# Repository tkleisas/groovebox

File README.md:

# groovebox — ВОКОИТЕР / ΟΡΓΑΝΟ

**Mission:** an open hardware and software groovebox that can be serviced
indefinitely. If a subsystem becomes unavailable, an equivalent one can be
substituted without discarding the panel, power system, enclosure, or
software. The reference brain is a **Raspberry Pi Zero 2W** on a replaceable
carrier, running the [yawn](https://github.com/tkleisas/yawn) audio engine;
a **Raspberry Pi Pico** panel module presents the whole control surface to
the brain as a plain USB-MIDI device.

Each SBC gets its own brain carrier and its own validated software profile;
the panel, power board, battery, and enclosure are the common platform. See
[`docs/mission.md`](docs/mission.md) for the mission, support tiers, and the
honest path for future Radxa/Orange Pi carriers.

Design language: Soviet-cosmonaut mission control per
[bokontep.gr](https://www.bokontep.gr) — deep-red faceplate, cream/black
keys, bilingual Greek/Cyrillic UI strings, terminal-green telemetry.

*Exploded NSR-1 rev B2 assembly, rendered in Blender. More views and the
[15-second detail animation](docs/renders/nsr1_animation.mp4):
[`docs/renders/`](docs/renders/).*

## Two designs, one repo

| | NSR-1 (ΟΡΓΑΝΟ 1) | NSR-2 |
|---|---|---|
| Concept | full-size panel, 400 × 170 mm | compact, 180 × 210 mm faceplate PCB |
| Keys | 55 MX keys (piano + 16-step row + function) | 45 Choc keys (4×8 grid) + 13 function |
| Control | 8 encoders, 2 pots, data slider, thumbstick | 4 encoders, thumbstick, crossfader |
| Status | **active target.** rev B2 control/keyboard verified; Pi brain carrier routed; power board routed except four rev A airwires | **deferred.** schematic-complete reference design; not the current build |
| Docs | [`docs/design.md`](docs/design.md) + [`hardware/README.md`](hardware/README.md) | [`docs/nsr2-design.md`](docs/nsr2-design.md) + [`nsr2/README.md`](nsr2/README.md) |

## What it does (emulator, today)

- **4 tracks** × **1–256 step patterns** (default 16, 16-step paged window).
  Per-step: on/off, velocity (data slider), accent (black keys), pitch and
  gate (hold-step + encoders, synth track).
- **Play mode**: the keyboard row becomes a 2-octave chromatic keyboard,
  velocity from the slider, joystick = pitch bend / mod. REC-arm + play
  records quantized notes into the pattern. On **drum tracks**
  (DrumSynth/DrumRack/DrumSlop) the 27 keys instead walk the
  instrument's drum voices left→right (whites and interleaved blacks as
  one physical strip, position modulo voice count — wraps at the end,
  so every key always sounds); toasts show the voice name.
- **Sound**: yawn engine instruments (SubtractiveSynth, DrumRack, FM,
  Wavetable, Granular, …) + one insert FX slot per track (29 effect types).
- **Sampling**: SAMPLE page — record from mic/line-in, trim, normalize,
  assign to a drum pad; LOAD page browses samples.
- **Controls (NSR-1 rev B2)**: 2 dedicated pots (filter cutoff/resonance),
  8 encoders with push (4 pageable + 4 amp-ADSR), data slider, 2-axis
  spring-return thumbstick, transport, MODE, </>, 4 soft keys, dual SHIFT
  keys at the keyboard row ends, dedicated 16-step row.
- **UI**: Elektron-style monochrome, 3 themes (mono / red / green phosphor),
  ПОЕХАЛИ! boot splash, full widget library (sequencer, mixer, waveform,
  ADSR, FM-algo, spectrum, phase pie, tuner, file browser, virtual keyboard…).
- **Sync/IO**: DIN MIDI in/out, Ableton Link (engine), USB-MIDI on OTG,
  integrated mic + line in for sampling (WM8731 codec).

## Hardware (NSR-1, rev B2)

| | |
|---|---|
| Brain | Raspberry Pi Zero 2W on the first SBC-specific carrier; separate carriers planned per SBC |
| Panel controller | Raspberry Pi Pico — presents as USB-MIDI device `groovebox-panel` |
| Audio codec | Audio Injector Zero (WM8731: stereo out + mic/line in) on the Pi carrier. Bench rig: CJMCU-1334 (UDA1334A, playback only) |
| Display | 4.0" SPI TFT 480×320 (ILI9488); UI rendered at 240×160, 2× integer scale |
| Keys | 55 MX-style switches (Gateron Red / Silent Red), hot-swap sockets, 32 LEDs, 19.05 mm pitch |
| Panel I/O | 5× MCP23017 (55 keys + 8 encoder pushes), HT16K33 (32 LEDs), 2× ADS1115 (2 pots + slider + joystick) |
| Power | Separate 1S power/battery board (USB-C charger, power path, 5V/3A boost, fuel gauge); 5000 mAh target |
| Panel size | 400×170 mm, deep red |

Full hardware design, GPIO maps and BOM: [docs/design.md](docs/design.md).
New platform board specs: [Pi Zero 2W brain carrier](hardware/brain/netlist-spec.md)
and [power/battery board](hardware/power/netlist-spec.md).
Panel/brain protocol (USB-MIDI + SysEx config):
[docs/panel-protocol.md](docs/panel-protocol.md).

### NSR-1 PCB views

Bare-board 3D renders, top and bottom, for all four NSR-1 boards. Headers
and connectors carry silkscreen pin numbers; the Pico header also has GPIO
names. The Pi carrier and power board are rev A; the power board still has
four open airwires (two `BAT_NEG`, two `SCL`). Full-size images are in
[`docs/renders/pcb/`](docs/renders/pcb/).

| Board | Top | Bottom |
|---|---|---|
| Control |  |  |
| Keyboard |  |  |
| Pi brain carrier |  |  |
| Power/battery |  |  |

## ElectroMechanicalDesigner integration

The NSR-1 hardware is imported and validated with
[**ElectroMechanicalDesigner (EMD)**](https://github.com/tkleisas/ElectroMechanicalDesigner):

- `hardware/tools/export_netlist.py` exports KiCad XML netlists.
- `hardware/tools/verify_emd.py` imports all four netlists and routed PCBs
  (control, keyboard, Pi carrier, power), validates them, and builds a combined
  **237-part / 735-connection** project.
- The combined project is placed in the 400 × 170 mm panel envelope and its
  package is verified with `emd package verify`.
- Generated projects/packages live in `hardware/emd-packages/` (gitignored);
  regenerate with
  `python3 hardware/tools/verify_emd.py --combined hardware/emd-packages/groovebox.json --package-dir hardware/emd-packages`.

EMD also validates the KiCad ERC/DRC flow, mounting-hole mechanical ports, and
fabrication exports used by this repo.

## Architecture

```
  Pi Zero 2W on brain carrier             Pico (panel module)
  ├ yawn engine (I2S codec)      ◄─USB─►  ├ keys    (5× MCP23017)
  ├ fbdev UI → 480×320 SPI TFT            ├ LEDs    (HT16K33)
  ├ DIN MIDI in/out (UART)                ├ encoders (GPIO)
  └ mic (codec input)                     └ analog  (2× ADS1115)
            ▲ 5V / power signals
            │
  Power/battery board — USB-C charge, 1S pack, gauge, 5V boost
```

The panel is deliberately dumb — it reports physical events and accepts
routing SysEx; **all musical semantics live in the brain app**. The same
app binary runs on the PC (SDL3 emulator with a geometry-driven,
mouse-interactive virtual front panel) and on the Pi (fbdev + panel over
USB-MIDI) through a HAL, which is how everything is developed before
hardware exists. See [`docs/panel-protocol.md`](docs/panel-protocol.md)
for the wire protocol.

## Building

| Target | How | Needs |
|---|---|---|
| Emulator | CMake in `emulator/` (binary `groovebox_sim`) | MSVC or GCC, SDL3, yawn submodule (`git submodule update --init`) |
| Panel firmware | `panel-fw/build.ps1` or CMake with the Pico SDK (see `panel-fw/README.md`) | Pico SDK + toolchain |
| OS image | Raspberry Pi OS Lite + `os-image/customize/` (first-run script, systemd unit) | a Pi / imager |
| Hardware | KiCad 10; NSR-1 and NSR-2 schematics are **generated** — see [`hardware/README.md`](hardware/README.md) and [`nsr2/README.md`](nsr2/README.md) before touching them | KiCad 10.0+ |

Windows/MSVC emulator build:

```bash
CMAKE="/c/Program Files/Microsoft Visual Studio/2022/Community/Common7/IDE/CommonExtensions/Microsoft/CMake/CMake/bin/cmake.exe"
"$CMAKE" -B emulator/build -S emulator -G "Visual Studio 17 2022" -A x64
"$CMAKE" --build emulator/build --target groovebox_sim --config Debug -- -m
emulator/build/Debug/groovebox_sim.exe            # interactive sim
```

The yawn engine is built lean (VST3 / NAM / Link / 3D / ONNX / video OFF).

### Pi cross-build (arm64, Docker)

`tools/build-pi-arm64.sh` builds `groovebox_sim` for 64-bit Raspberry Pi
OS (bookworm, aarch64) in a Docker container — no Pi needed on the desk:

```bash
tools/build-pi-arm64.sh     # image + cross-build + provenance + qemu smoke
```

The image (`emulator/pi/Dockerfile`) is Debian bookworm with the
`aarch64-linux-gnu` toolchain and the **arm64** `libasound2-dev` (ALSA is
the one target-arch dependency — RtMidi and PortAudio are compiled from
source by yawn's FetchContent but link against the target's ALSA). The
toolchain file is `emulator/pi/aarch64-toolchain.cmake`; CMake is driven
with `-DGB_PI_BACKEND=ON`, which swaps the SDL3 SimBackend for the
headless PiBackend (fbdev + RtMidi) and drops the SDL3 link. The script
finishes by proving the binary (`readelf -h` → `AArch64`) and
smoke-running it under `qemu-aarch64` (the container has no ALSA device
PortAudio accepts, so the engine can't boot there — the qemu run proves
execution + graceful peripheral degradation; `--profile` numbers need a
Pi with a codec or the Windows sim).

### Pi backend (PiBackend, `GB_PI_BACKEND=ON`)

- **Display**: fbdev — opens `/dev/fb1` (ILI9488 SPI TFT via fbtft
  overlay), falls back to `/dev/fb0`, mmaps the framebuffer and writes
  the 240×160 RGB565 UI frame 2×-doubled (480×320), centered. 16 bpp
  writes through; 32 bpp (XRGB8888) converts per pixel.
- **Panel in**: RtMidi input on the port named `groovebox-panel`,
  decoded per [`docs/panel-protocol.md`](docs/panel-protocol.md)
  (channel 1: notes 36–91 → keys, CC 20/21 pots, CC 26 slider, CC 1
  joystick Y, CC 16–23 encoder deltas, CC 32–39 encoder push,
  pitch bend → joystick X).
- **LEDs**: note on/off on channel 2 back to the panel.
- Neither peripheral is fatal — a Pi booted without the panel or the
  display logs a warning and keeps the engine running (CI / profiling).
- SIGINT/SIGTERM route to the app's quit path, so the systemd unit or
  Ctrl-C shuts the engine down cleanly.

Deployment note: the arm64 binary dynamically links `libportaudio.so.2`
(yawn builds PortAudio shared). Ship `emulator/build-pi-arm64/lib/libportaudio.so.2`
alongside the binary (e.g. in `/usr/local/lib` + `ldconfig`, or next to
the binary with an rpath). `libasound.so.2` is part of Raspberry Pi OS.

### Heavy-load profiling (`--profile`)

```
groovebox_sim --profile 10
```

Worst-case musical load for the Zero 2W gate: all 4 tracks programmed on
all 16 steps (vel 120), 140 BPM, a reverb inserted on T1+T2, transport
rolling, UI rendering every frame. Prints PortAudio CPU% and the
PortAudio callback status flags (xrun bits) once per second, then exits
0. Runs on every backend (Windows sim, Pi hardware, qemu).

### Interactive controls (sim)

- **Mouse** (panel view): click keys/buttons; drag pots & slider; 2D-drag
  joystick (springs back); wheel over encoders; click encoder = push.
- **PC keyboard**: Z-row + Q-row = piano whites (with standard black-key
  letters/digits), Space = play/stop, Enter = rec, Tab = MODE,
  arrows = </>, F1–F4 = soft keys S1–S4, Shift = SHIFT, F5–F10 + `-`/`=` =
  pots, `[`/`]` = slider, F11 = panel/screen view, F12 = theme, ESC = quit.
- **Track select**: S3/S4 (TRK-/TRK+) or Shift + white keys 1–4;
  Shift + white 5–8 = mute.

### Drum editing (INST page on drum tracks)

For pad instruments (DrumSynth / DrumRack / DrumSlop) the INST page
edits the **last-played pad**: hitting a key in play mode (or a
hold-step voice p-lock) makes that voice the edit pad — the header
shows it (`SNARE T1 140`), an `EDIT SNARE` toast confirms, and all
bindings rebuild to that voice. Sequencer playback never steals the
edit focus.

- **Encoder pages**: PAD / PAD2 = the edited pad's params (DrumSynth:
  Tune/Drive, kick adds Sine/White/Pink; DrumRack: Pad Vol/Pan/Pitch/
  Choke/Start/End; DrumSlop: Pad Vol/Pan/Pitch/Rev/Cutoff/Reso),
  KIT = instrument globals (Volume, OS 2×, slice controls). S2 = PG+
  cycles them.
- **Macro encoders 5–8** (factory binding): A/D = the edited pad's
  attack/decay (S/R also bound on DrumSlop). Pots stay inert on
  DrumSynth/DrumRack (CUT/RES bind only where the instrument exposes
  them — DrumSlop pads).
- DrumSynth has no selected-slot concept — its 36 params are globally
  indexed per voice (kick = 7 @ index 0, others = 4 @ 7+(slot−1)·4),
  so the edit pad is pure index arithmetic; DrumRack/DrumSlop get the
  pad via their `selectedPad` setter.

### Scripted test / asset modes

```
groovebox_sim --smoke       engine boot + notes self-test
groovebox_sim --uitest      UI interaction assertions (8/8)
groovebox_sim --seqtest     sequencer scheduling assertions (6/6)
groovebox_sim --longtest    1–256 step pattern assertions (9/9)
groovebox_sim --paramtest   pot pickup / encoder ownership / FX (11/11)
groovebox_sim --sampletest  mic capture → trim → assign → browser (8/8)
groovebox_sim --panelprobe  synthetic mouse → HAL events (3/3)
groovebox_sim --panel=nsr2 --nsr2test    NSR-2 grid semantics (6/6)
groovebox_sim --revbtest    NSR-1 rev B: step row, p-lock, scale lock (6/6)
groovebox_sim --macrotest   macro encoder assign/bind/reset/persist (6/6)
groovebox_sim --tracktest   engine tracks, INST swap, MFX, type toggle (4/4)
groovebox_sim --bouncetest  clip record, bounce, FX slot 2 (7/7)
groovebox_sim --drumtest    drum key map: voices, wrap, p-lock (9/9)
groovebox_sim --padtest     last-played-pad edit focus (8/8)
groovebox_sim --panel=nsr2 --panelprobe  synthetic mouse on NSR-2 (3/3)
groovebox_sim --widgets     widget showcase → docs/widgets.png
groovebox_sim --profile 10  heavy-load profiling: CPU% + xrun flags/s
groovebox_sim --fontchart   font chart → docs/fontchart.png
groovebox_sim --themes      3-theme chart → docs/themes.png
groovebox_sim --paneldump   panel render → docs/panel_sim.png
groovebox_sim --splashdump  boot splash → docs/bootsplash.png
```

`--panel=<nsr1|nsr2>` selects the panel profile (faceplate, key
semantics, LED count) for interactive, test, and dump modes
(`--panel=nsr2 --paneldump panel.png` renders the NSR-2 faceplate).

## Repository layout

| Path | What it is |
|---|---|
| `docs/` | design documents: mission/strategy (`mission.md`), NSR-1 `design.md`, panel ↔ brain protocol (`panel-protocol.md`), NSR-2 `nsr2-design.md`, mockups & generated charts |
| `emulator/` | the groovebox app + device emulator (`hal.h`, SimBackend = SDL3 desktop, PiBackend = headless Pi fbdev+RtMidi, PanelView, ui, widgets, font5x7, pattern…), `pi/` = arm64 cross-build (Dockerfile + toolchain) |
| `panel-fw/` | Raspberry Pi Pico firmware (TinyUSB USB-MIDI panel controller, protocol v1 + GRV SysEx config) |
| `hardware/` | **active NSR-1 platform:** control/keyboard, Pi carrier, power board, enclosure/faceplate, and ElectroMechanicalDesigner integration/package checks |
| `nsr2/` | the deferred NSR-2 compact reference design: netlist spec, generated KiCad schematics, footprint library, enclosure spec, mockup |
| `os-image/` | Raspberry Pi OS Lite customization — boots straight into the app (~10 s to sound) |
| `tools/` | mockup generators (panel, UI), rgb565 conversion |
| `yawn/` | the audio engine (git submodule) |

## Status & roadmap

NSR-1 is the active hardware target. The rev B2 control and keyboard
boards are routed, DRC-clean, and EMD-verified. Next: the Raspberry Pi Zero
2W brain carrier, the separate power/battery board, and the NSR-1 enclosure
update for both. NSR-2 is retained as a schematic-complete reference but is
deferred; it is not the current build.

Software milestones (emulator-first):

- **M1 done** — emulator skeleton: engine headless on PC, HAL, sim window,
  font (Latin/Greek/Cyrillic + symbols), 26 widgets.
- **M2 done** — full instrument in the emulator: live step sequencer
  (1–256 steps), play mode, per-step pitch/gate, virtual front panel,
  themes, boot splash, pot pickup, encoder parameter pages, FX page,
  SAMPLE/LOAD/SETTINGS pages, dialogs. M2d adds one engine track per UI
  track (engine-level mutes, per-track FX), INST page (instrument
  picker with full param rebind), MFX page (MIDI-effect slot), TRACK
  page (channel type MIDI/AUDIO + vol/pan/input/monitor), macro
  encoders (assignable, persisted). AUDIO tracks record input into
  looping clips (REC arm + PLAY/STOP); BOUNCE renders a MIDI track's
  pattern offline to a WAV + looping clip on the first AUDIO track.
  FX page has two insert slots per track (shift+S2 switches).
- **M3 done** — Pi software path: headless PiBackend (fbdev 2× display +
  RtMidi panel per `docs/panel-protocol.md`) behind `-DGB_PI_BACKEND=ON`,
  Docker arm64 cross-build (`tools/build-pi-arm64.sh`, ELF64 AArch64
  verified), `--profile N` heavy-load harness (4 tracks dense, 140 BPM,
  reverb ×2, per-second CPU% + xrun flags).
- **M4** — bench rig: codec, panel firmware on real hardware, display.
- **M5 in progress** — battery, enclosure, rev B2 routed PCBs, and the verified EMD assembly package. The NSR-1 brain carrier and power board are the current hardware work.

## Conventions

- Commit messages: `area: summary` (`panel-fw:`, `os-image:`, `nsr2:`, `docs:`).
- Generated files are marked as such in their directories — read
  [`hardware/README.md`](hardware/README.md) and
  [`nsr2/README.md`](nsr2/README.md) before hand-editing generated
  schematics.
- Per-device credentials never enter the repo (see `os-image/customize/`).
- License: MIT (see [`LICENSE`](LICENSE)). Vendored third-party hardware
  libraries keep their own licenses — see the footprints table in
  [`nsr2/README.md`](nsr2/README.md).

ПОЕХАЛИ!

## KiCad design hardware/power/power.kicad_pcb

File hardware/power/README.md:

# NSR-1 power/battery board

Source of truth: [`netlist-spec.md`](netlist-spec.md). This board is common to
the NSR-1 platform and future SBC carriers.

## Status

- `power.kicad_pcb` — 100 × 70 mm, 4-layer, 4× M3 holes; routed except four rev A airwires (two BAT_NEG, two SCL).
- `power.kicad_sch` — generated from `hardware/tools/gen_schematics.py`;
  0 ERC errors with expected embedded-symbol warnings.
- Power-board and battery bays are specified in
  [`../enclosure-spec.md`](../enclosure-spec.md).

## Checks

```bash
docker run --rm -v "$PWD:/work" -w /work \
  -e KICAD_SYMBOL_DIR=/usr/share/kicad/symbols kicad/kicad:10.0 \
  python3 hardware/tools/gen_schematics.py power
docker run --rm -v "$PWD:/work" -w /work \
  -e KICAD_SYMBOL_DIR=/usr/share/kicad/symbols kicad/kicad:10.0 \
  python3 hardware/tools/export_netlist.py --board power
cd hardware/power
kicad-cli sch erc power.kicad_sch --output /tmp/power-erc.json --format json --severity-all
kicad-cli pcb drc power.kicad_pcb --output /tmp/power-drc.json --format json --severity-all
```

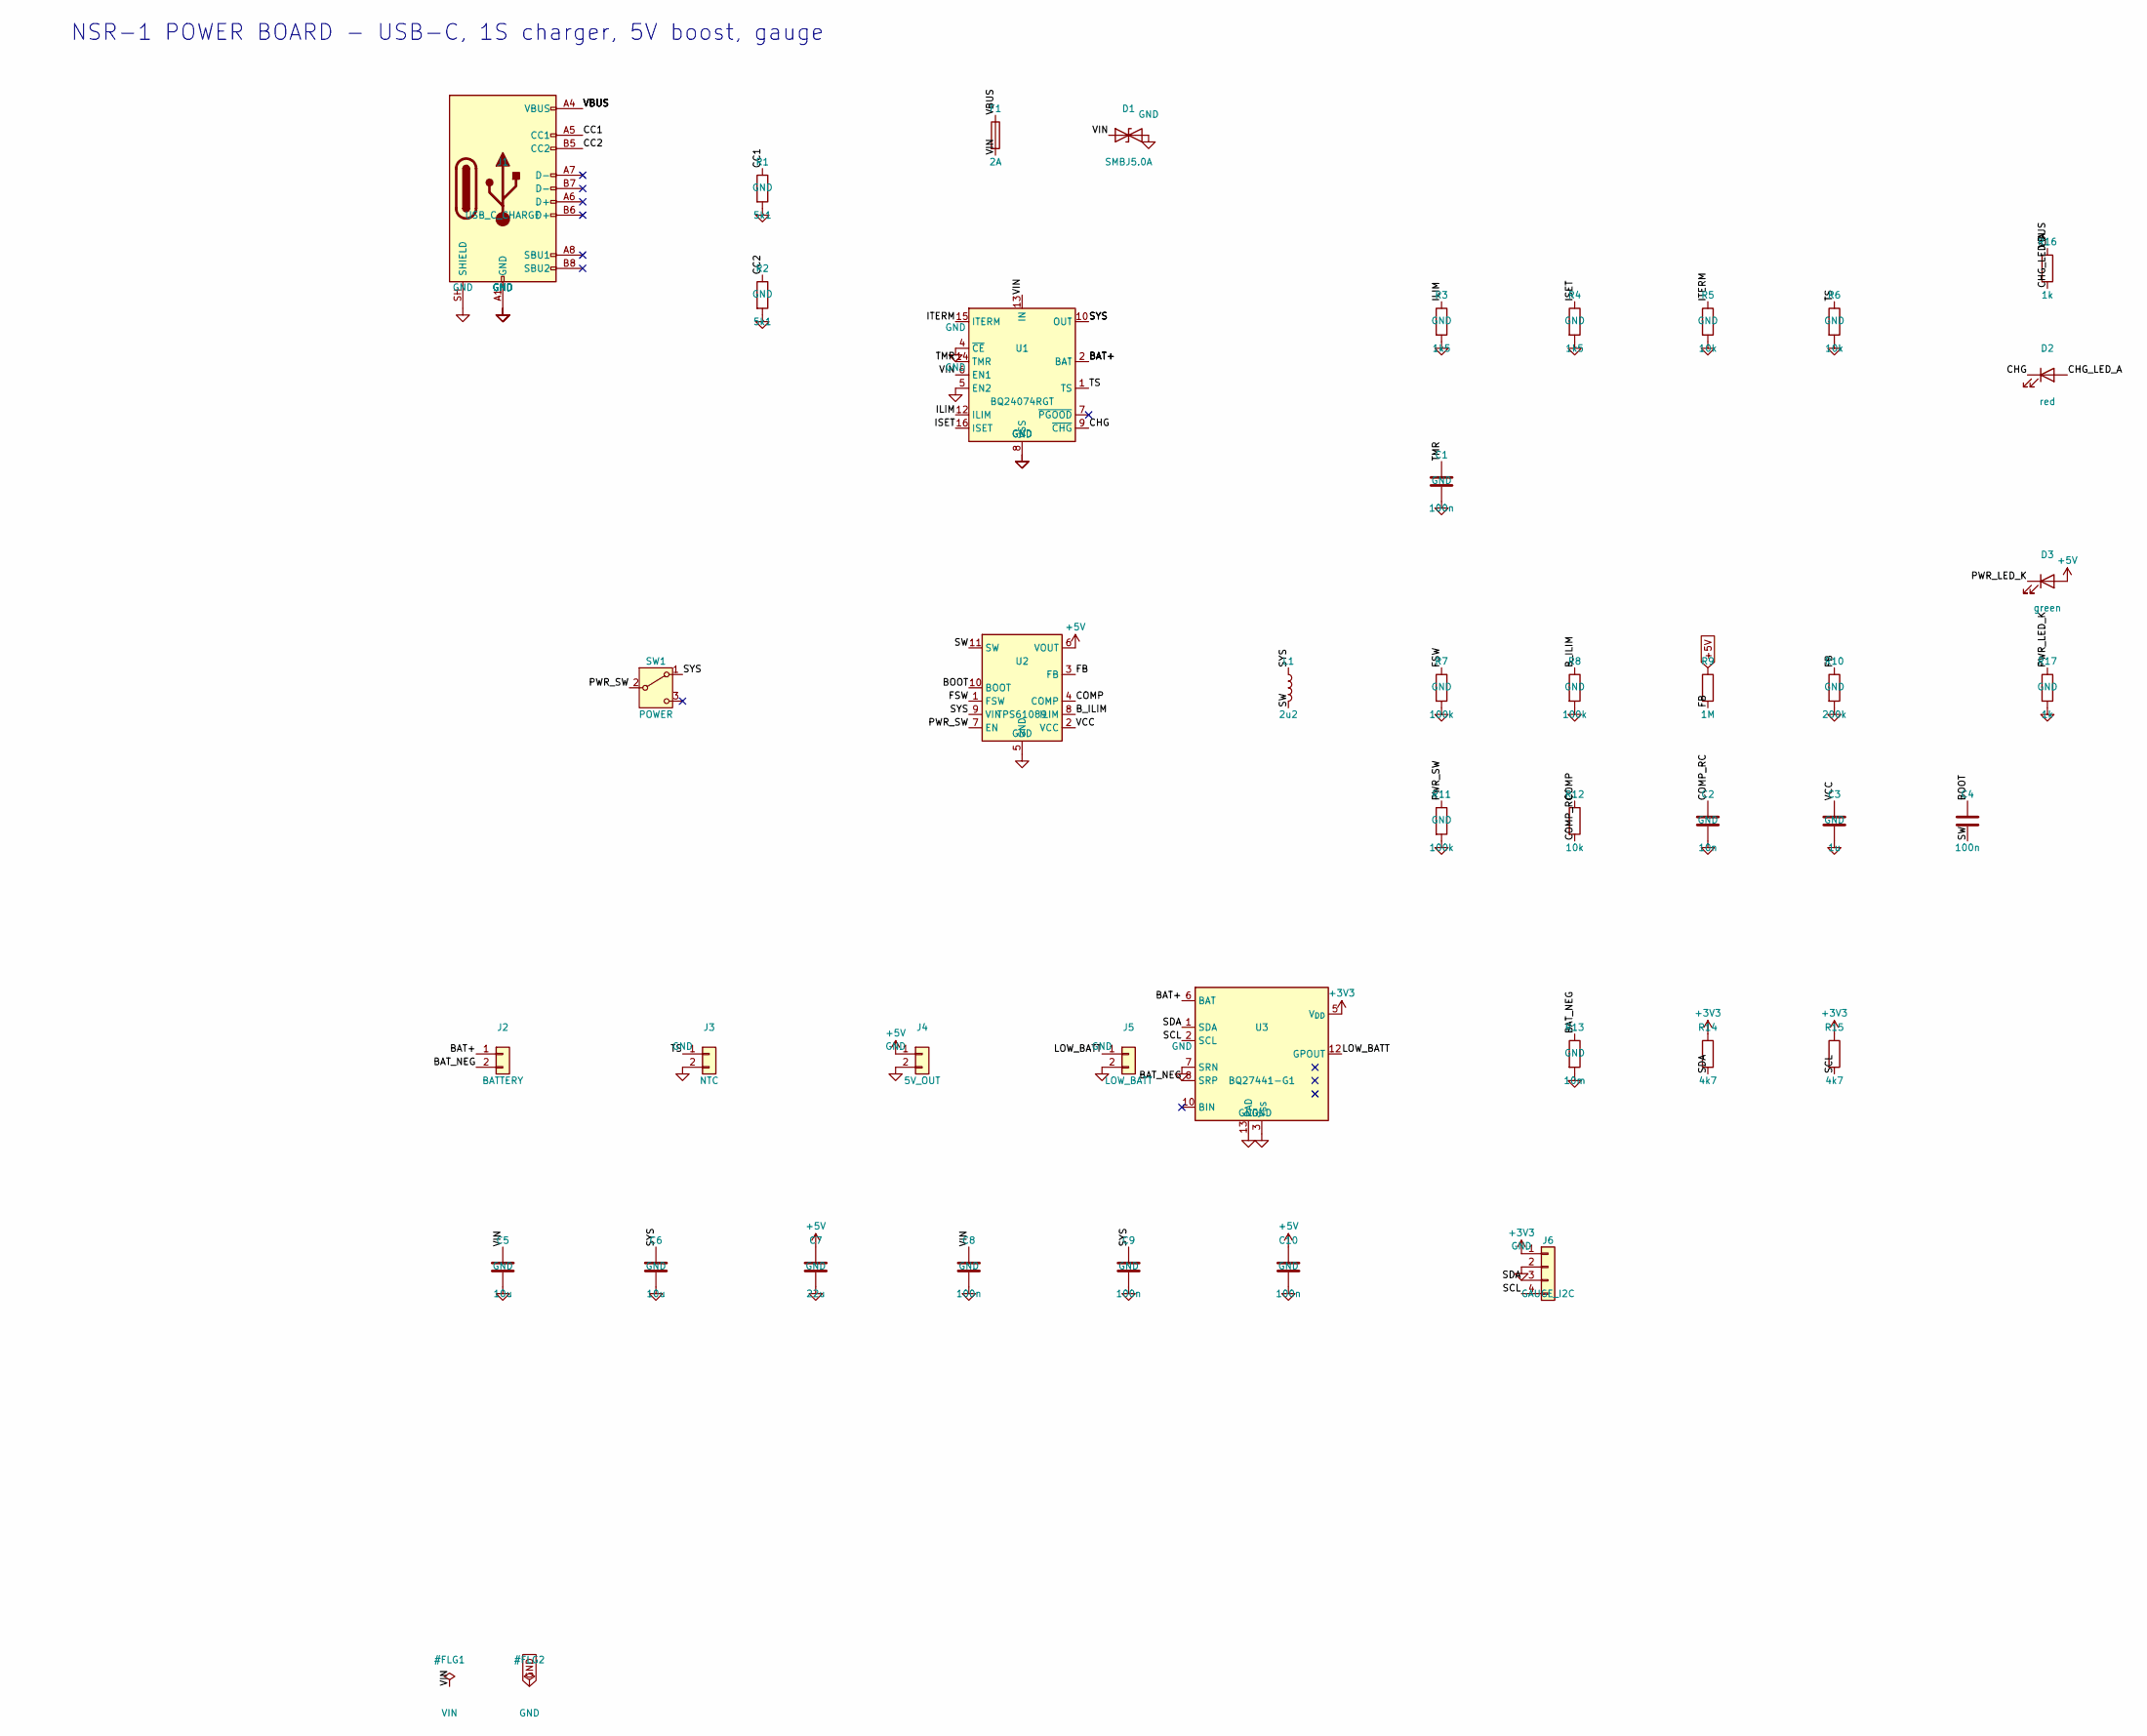
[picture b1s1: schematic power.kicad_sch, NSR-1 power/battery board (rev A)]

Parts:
C1, C4, C8, C9, C10: 100n; C_0805_2012Metric
C2: 10n; C_0805_2012Metric
C3: 1u; C_1206_3216Metric
C5, C6: 10u; C_1206_3216Metric
C7: 22u; C_1206_3216Metric
D1: SMBJ5.0A; D_SMB
D2: red; LED_0805_2012Metric
D3: green; LED_0805_2012Metric
F1: 2A; Fuse_1206_3216Metric
J1: USB_C_CHARGE; USB_C_Receptacle_GCT_USB4105-xx-A_16P_TopMnt_Horizontal
J2: BATTERY; AMASS_XT30UPB-F_1x02_P5.0mm_Vertical
J3: NTC; JST_XH_B2B-XH-A_1x02_P2.50mm_Vertical
J4: 5V_OUT; JST_XH_B2B-XH-A_1x02_P2.50mm_Vertical
J5: LOW_BATT; JST_XH_B2B-XH-A_1x02_P2.50mm_Vertical
J6: GAUGE_I2C; JST_XH_B4B-XH-A_1x04_P2.50mm_Vertical
L1: 2u2; L_Coilcraft_XAL7030-222
R1, R2: 5k1; R_0805_2012Metric
R3, R4: 1k5; R_0805_2012Metric
R5, R6, R12: 10k; R_0805_2012Metric
R7, R8, R11: 100k; R_0805_2012Metric
R9: 1M; R_0805_2012Metric
R10: 200k; R_0805_2012Metric
R13: 10m; R_2512_6332Metric
R14, R15: 4k7; R_0805_2012Metric
R16, R17: 1k; R_0805_2012Metric
SW1: POWER; SW_Slide_SPDT_Straight_CK_OS102011MS2Q
U1: BQ24074RGT; VQFN-16-1EP_3x3mm_P0.5mm_EP1.6x1.6mm
U2: TPS61089; Texas_VQFN-RNR0011A-11
U3: BQ27441-G1; Texas_S-PDSO-N12

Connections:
+3V3: J6.1, R14.1, R15.1, U3.5 (V_{DD})
+5V: C7.1, C10.1, D3.2 (A), J4.1, R9.1, U2.6 (VOUT)
BAT+: J2.1, U1.2 (BAT), U1.3 (BAT), U3.6 (BAT)
BAT_NEG: J2.2, R13.1, U3.8 (SRP)
BOOT: C4.1, U2.10 (BOOT)
B_ILIM: R8.1, U2.8 (ILIM)
CC1: J1.A5 (CC1), R1.1
CC2: J1.B5 (CC2), R2.1
CHG: D2.1 (K), U1.9 (~CHG)
CHG_LED_A: D2.2 (A), R16.2
COMP: R12.1, U2.4 (COMP)
COMP_RC: C2.1, R12.2
FB: R9.2, R10.1, U2.3 (FB)
FSW: R7.1, U2.1 (FSW)
GND: C1.2, C2.2, C3.2, C5.2, C6.2, C7.2, C8.2, C9.2, C10.2, D1.2 (A2), J1.A1 (GND), J1.A12 (GND), J1.B1 (GND), J1.B12 (GND), J1.SH (SHIELD), J3.2, J4.2, J5.2, J6.2, R1.2, R2.2, R3.2, R4.2, R5.2, R6.2, R7.2, R8.2, R10.2, R11.2, R13.2, R17.2, U1.4 (~CE), U1.5 (EN2), U1.8 (VSS), U1.17 (VSS), U2.5 (GND), U3.3 (V_{SS}), U3.7 (SRN), U3.13 (PAD)
ILIM: R3.1, U1.12 (ILIM)
ISET: R4.1, U1.16 (ISET)
ITERM: R5.1, U1.15 (ITERM)
LOW_BATT: J5.1, U3.12 (GPOUT)
PWR_LED_K: D3.1 (K), R17.1
PWR_SW: R11.1, SW1.2 (B), U2.7 (EN)
SCL: J6.4, R15.2, U3.2 (SCL)
SDA: J6.3, R14.2, U3.1 (SDA)
SW: C4.2, L1.2, U2.11 (SW)
SYS: C6.1, C9.1, L1.1, SW1.1 (A), U1.10 (OUT), U1.11 (OUT), U2.9 (VIN)
TMR: C1.1, U1.14 (TMR)
TS: J3.1, R6.1, U1.1 (TS)
VBUS: F1.1, J1.A4 (VBUS), J1.A9 (VBUS), J1.B4 (VBUS), J1.B9 (VBUS), R16.1
VCC: C3.1, U2.2 (VCC)
VIN: C5.1, C8.1, D1.1 (A1), F1.2, U1.6 (EN1), U1.13 (IN)

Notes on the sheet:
NSR-1 POWER BOARD - USB-C, 1S charger, 5V boost, gauge

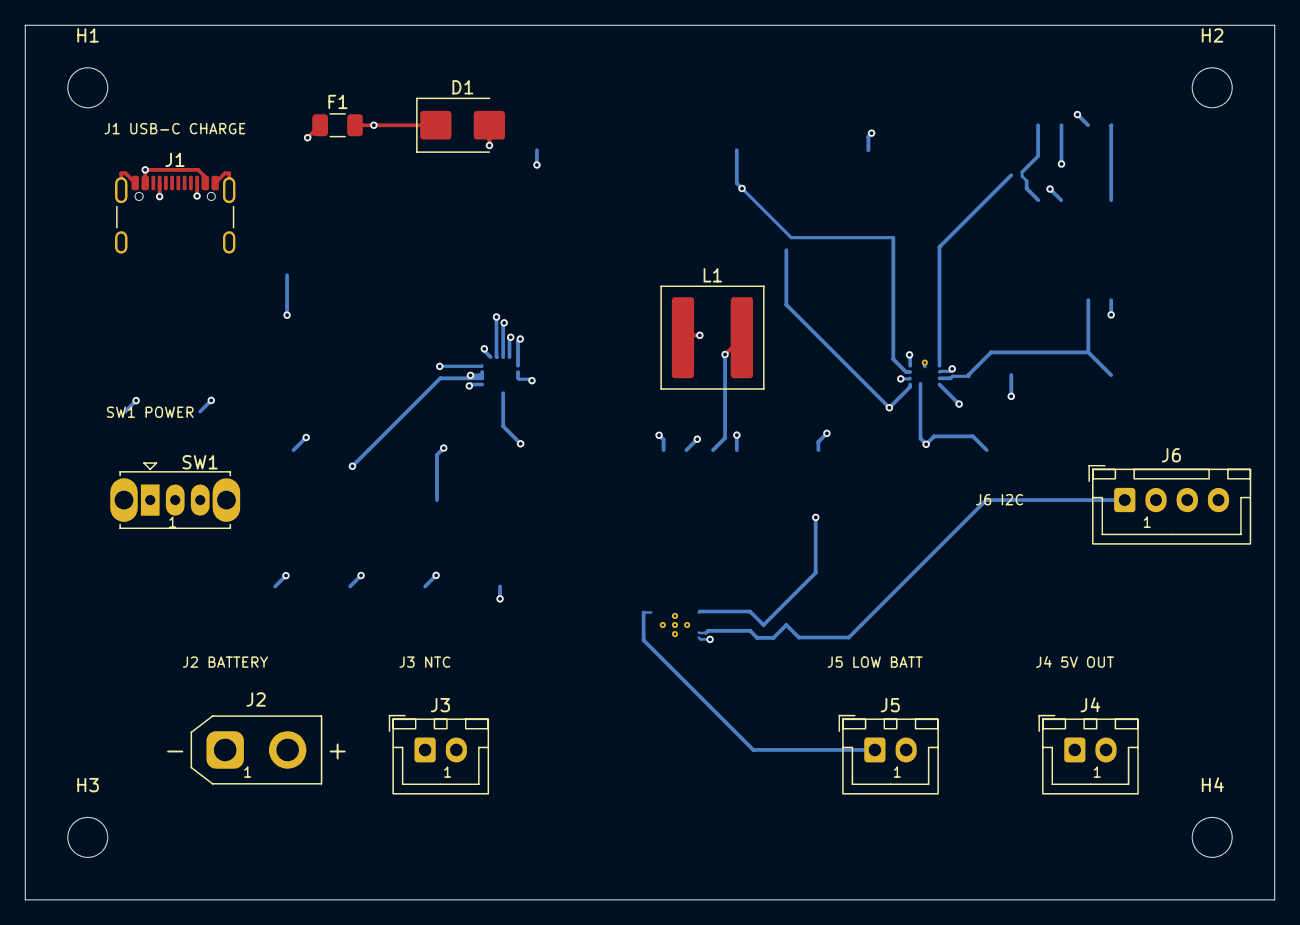
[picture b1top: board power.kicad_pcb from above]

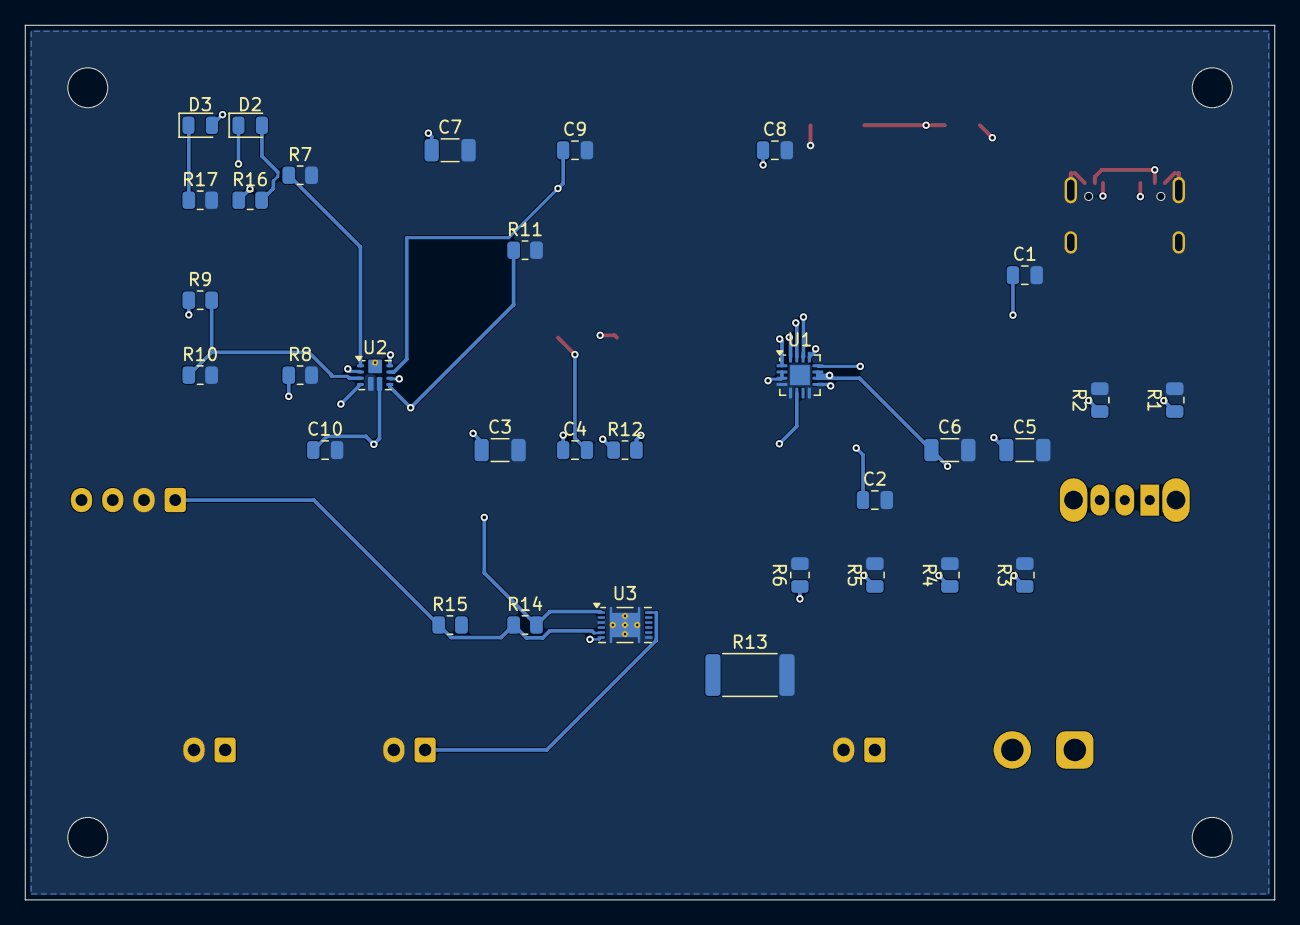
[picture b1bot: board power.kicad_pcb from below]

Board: 4 copper layers, 100.0 x 70.0 mm, 46 parts (32 on the bottom side), 30 nets.

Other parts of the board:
H1, H2, H3, H4: MountingHole_3.2mm_M3

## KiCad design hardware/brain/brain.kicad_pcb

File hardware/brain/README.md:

# NSR-1 brain carrier — Raspberry Pi Zero 2W

Source of truth: [`netlist-spec.md`](netlist-spec.md). This is the first
SBC-specific carrier; Radxa/Orange Pi carriers are separate boards.

## Generated files

- `brain.kicad_sch` — generated by `python3 hardware/tools/gen_schematics.py`.
  Do not hand-edit while the generator is active.
- `brain.kicad_pcb` — outline and mounting holes generated by
  `hardware/tools/make_platform_outlines.py`; the routed layout becomes
  hand-owned after the first placement.

## Checks

```bash
python3 hardware/tools/gen_schematics.py brain
python3 hardware/tools/export_netlist.py --board brain
cd hardware/brain
kicad-cli sch erc brain.kicad_sch --output /tmp/brain-erc.json --format json --severity-all
kicad-cli pcb drc brain.kicad_pcb --output /tmp/brain-drc.json --format json --severity-all
emd import kicad brain.net.xml --out /tmp/brain.json
emd validate /tmp/brain.json
```

Current status: schematic generated, 0 ERC errors (expected
`lib_symbol_mismatch` warnings only); netlist validates in EMD; PCB
110 × 90 mm, routed, 0 unconnected, 4× M3 holes.

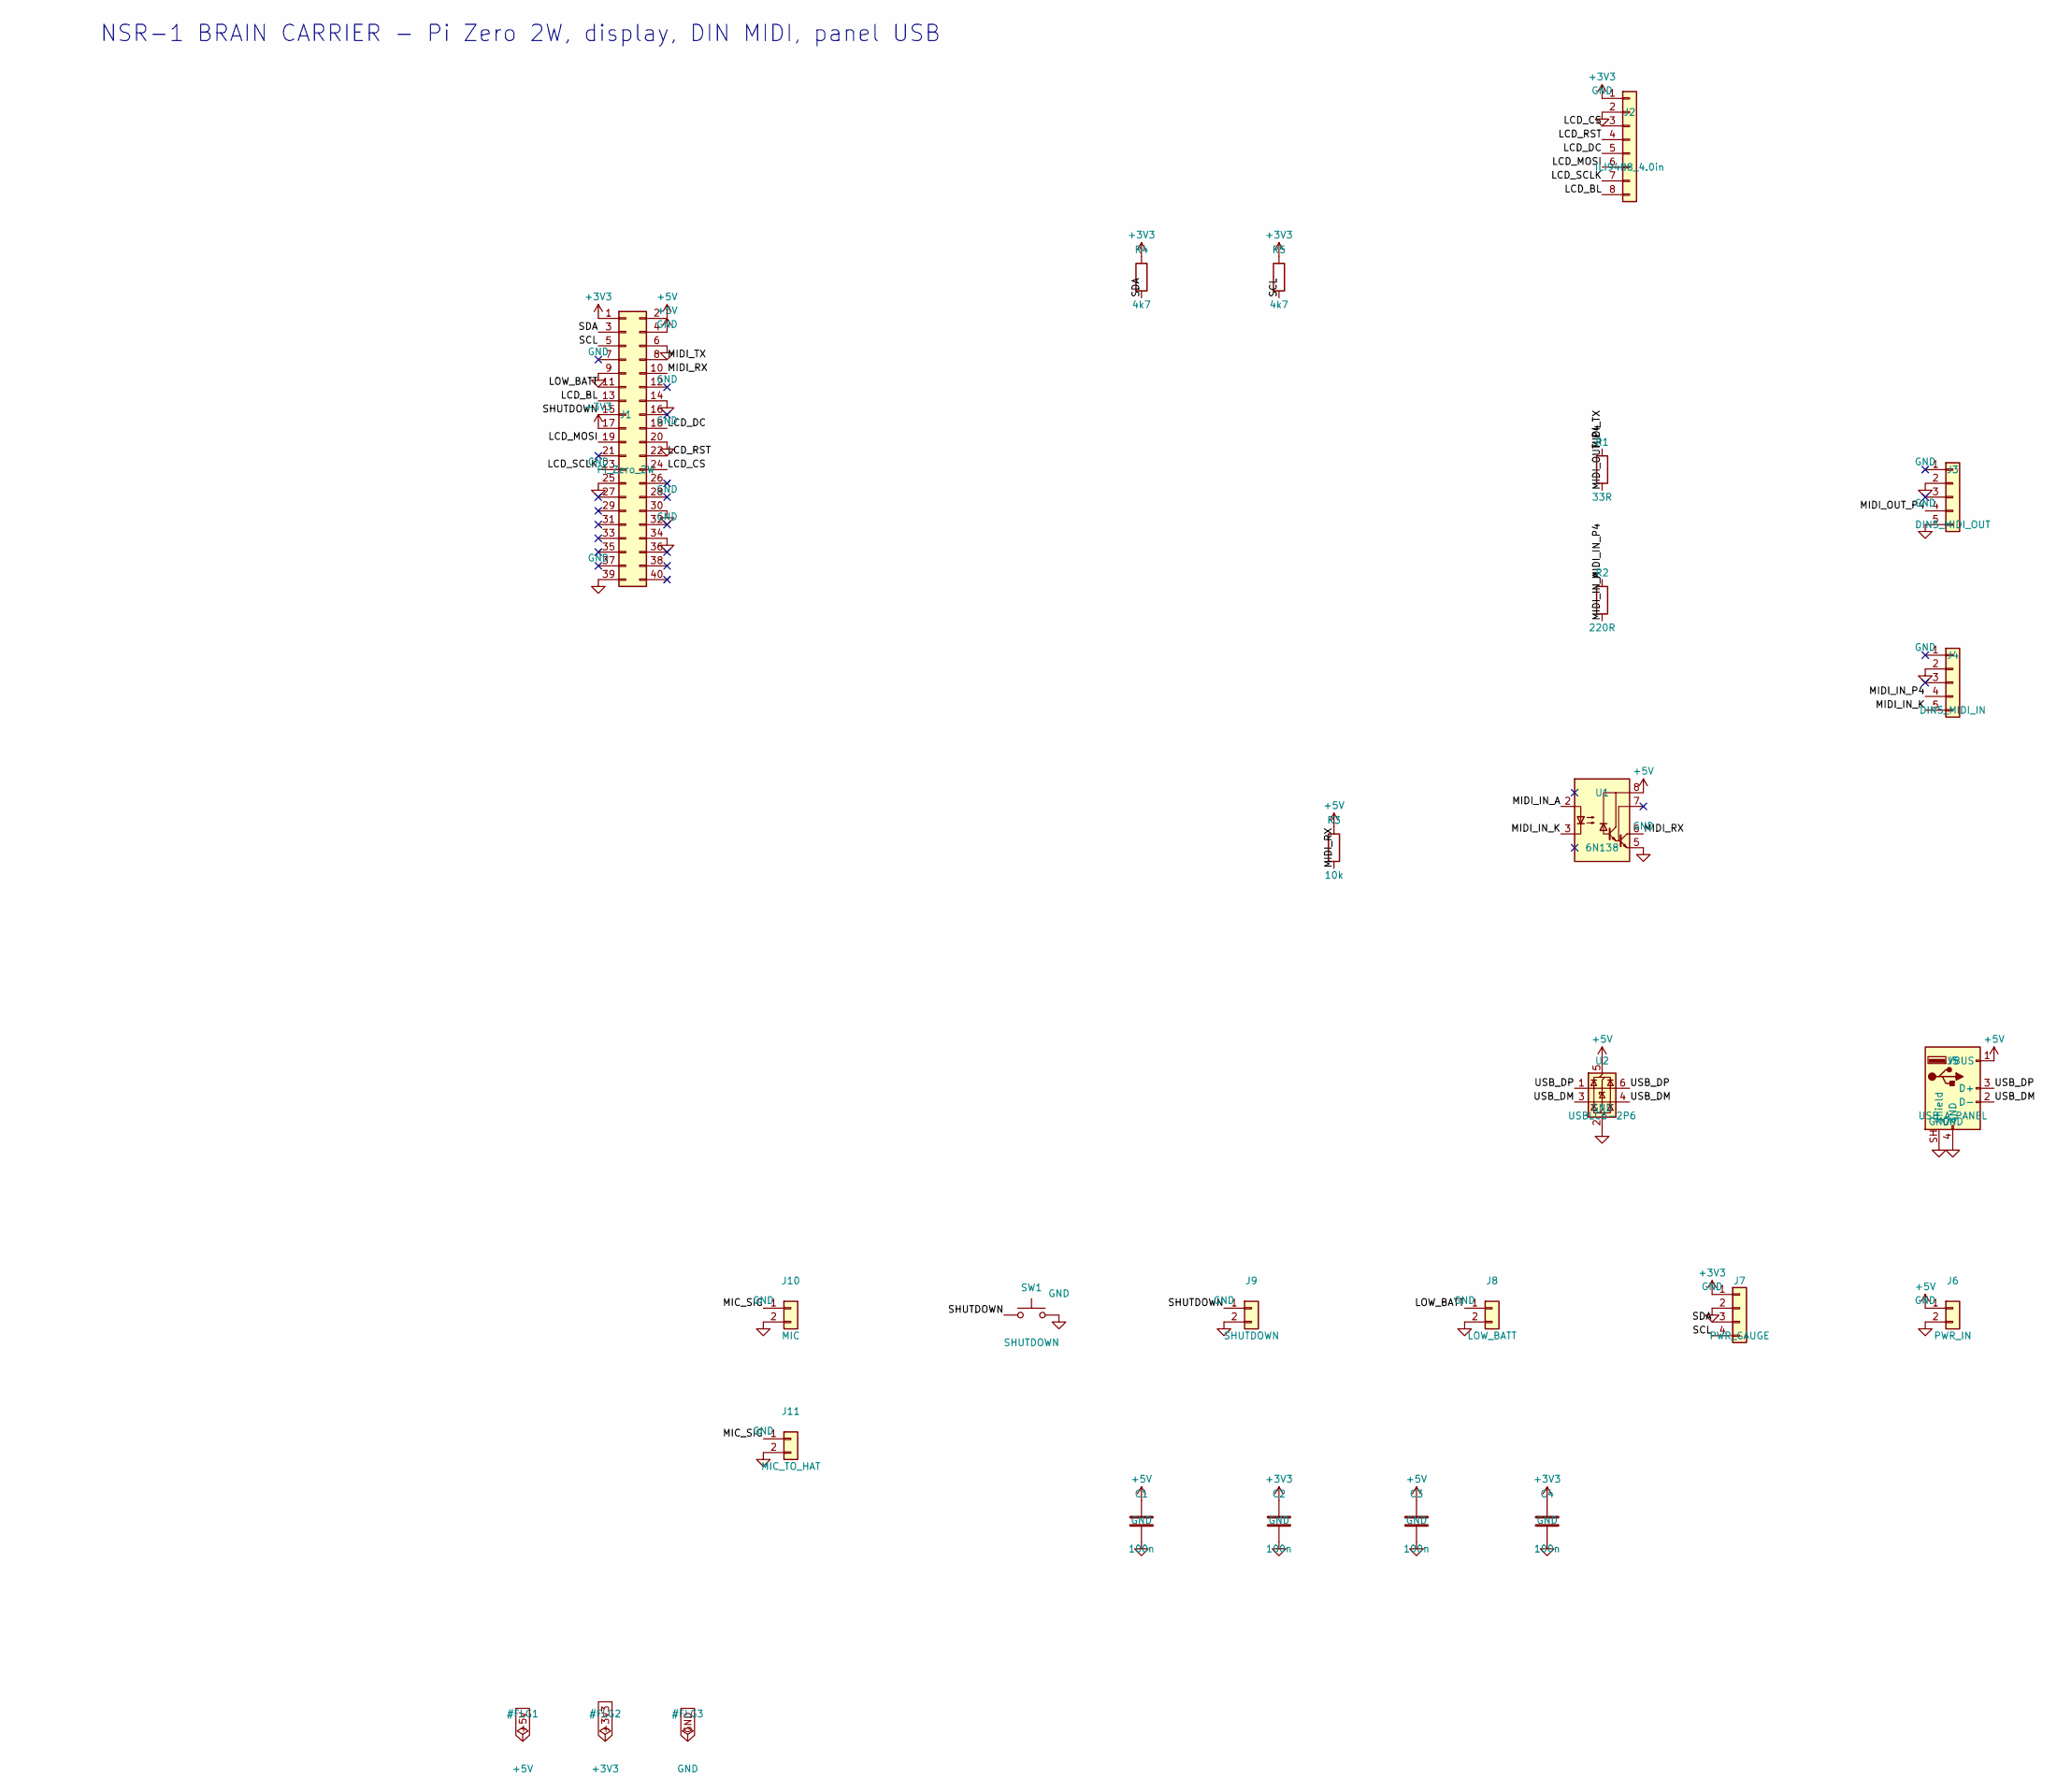
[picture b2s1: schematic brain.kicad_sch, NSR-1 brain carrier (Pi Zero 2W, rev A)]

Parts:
C1, C2, C3, C4: 100n; C_0805_2012Metric
J1: Pi_Zero_2W; Raspberry_Pi_Zero_Socketed_THT_FaceDown_MountingHoles
J2: ILI9488_4.0in; PinHeader_1x08_P2.54mm_Horizontal
J3: DIN5_MIDI_OUT; DIN5-RA-PTH
J4: DIN5_MIDI_IN; DIN5-RA-PTH
J5: USB_A_PANEL; USB_A_Connfly_DS1098_Horizontal
J6: PWR_IN; JST_XH_B2B-XH-A_1x02_P2.50mm_Vertical
J7: PWR_GAUGE; JST_XH_B4B-XH-A_1x04_P2.50mm_Vertical
J8: LOW_BATT; JST_XH_B2B-XH-A_1x02_P2.50mm_Vertical
J9: SHUTDOWN; JST_XH_B2B-XH-A_1x02_P2.50mm_Vertical
J10: MIC; JST_XH_B2B-XH-A_1x02_P2.50mm_Vertical
J11: MIC_TO_HAT; JST_XH_B2B-XH-A_1x02_P2.50mm_Vertical
R1: 33R; R_0805_2012Metric
R2: 220R; R_0805_2012Metric
R3: 10k; R_0805_2012Metric
R4, R5: 4k7; R_0805_2012Metric
SW1: SHUTDOWN; SW_PUSH_6mm
U1: 6N138; DIP-8_W7.62mm
U2: USBLC6-2P6; SOT-23-6

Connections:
+3V3: C2.1, C4.1, J1.1, J1.17, J2.1, J7.1, R4.1, R5.1
+5V: C1.1, C3.1, J1.2, J1.4, J5.1 (VBUS), J6.1, R3.1, U1.8 (VCC), U2.5 (VBUS)
GND: C1.2, C2.2, C3.2, C4.2, J1.6, J1.9, J1.14, J1.20, J1.25, J1.30, J1.34, J1.39, J2.2, J3.2, J3.5, J4.2, J5.4 (GND), J5.SH (Shield), J6.2, J7.2, J8.2, J9.2, J10.2, J11.2, SW1.2, U1.5 (GND), U2.2 (GND)
LCD_BL: J1.13, J2.8
LCD_CS: J1.24, J2.3
LCD_DC: J1.18, J2.5
LCD_MOSI: J1.19, J2.6
LCD_RST: J1.22, J2.4
LCD_SCLK: J1.23, J2.7
LOW_BATT: J1.11, J8.1
MIC_SIG: J10.1, J11.1
MIDI_IN_A: R2.2, U1.2 (C1)
MIDI_IN_K: J4.5, U1.3 (C2)
MIDI_IN_P4: J4.4, R2.1
MIDI_OUT_P4: J3.4, R1.2
MIDI_RX: J1.10, R3.2, U1.6 (VO2)
MIDI_TX: J1.8, R1.1
SCL: J1.5, J7.4, R5.2
SDA: J1.3, J7.3, R4.2
SHUTDOWN: J1.15, J9.1, SW1.1
USB_DM: J5.2 (D-), U2.3 (I/O2), U2.4 (I/O2)
USB_DP: J5.3 (D+), U2.1 (I/O1), U2.6 (I/O1)

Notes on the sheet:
NSR-1 BRAIN CARRIER - Pi Zero 2W, display, DIN MIDI, panel USB

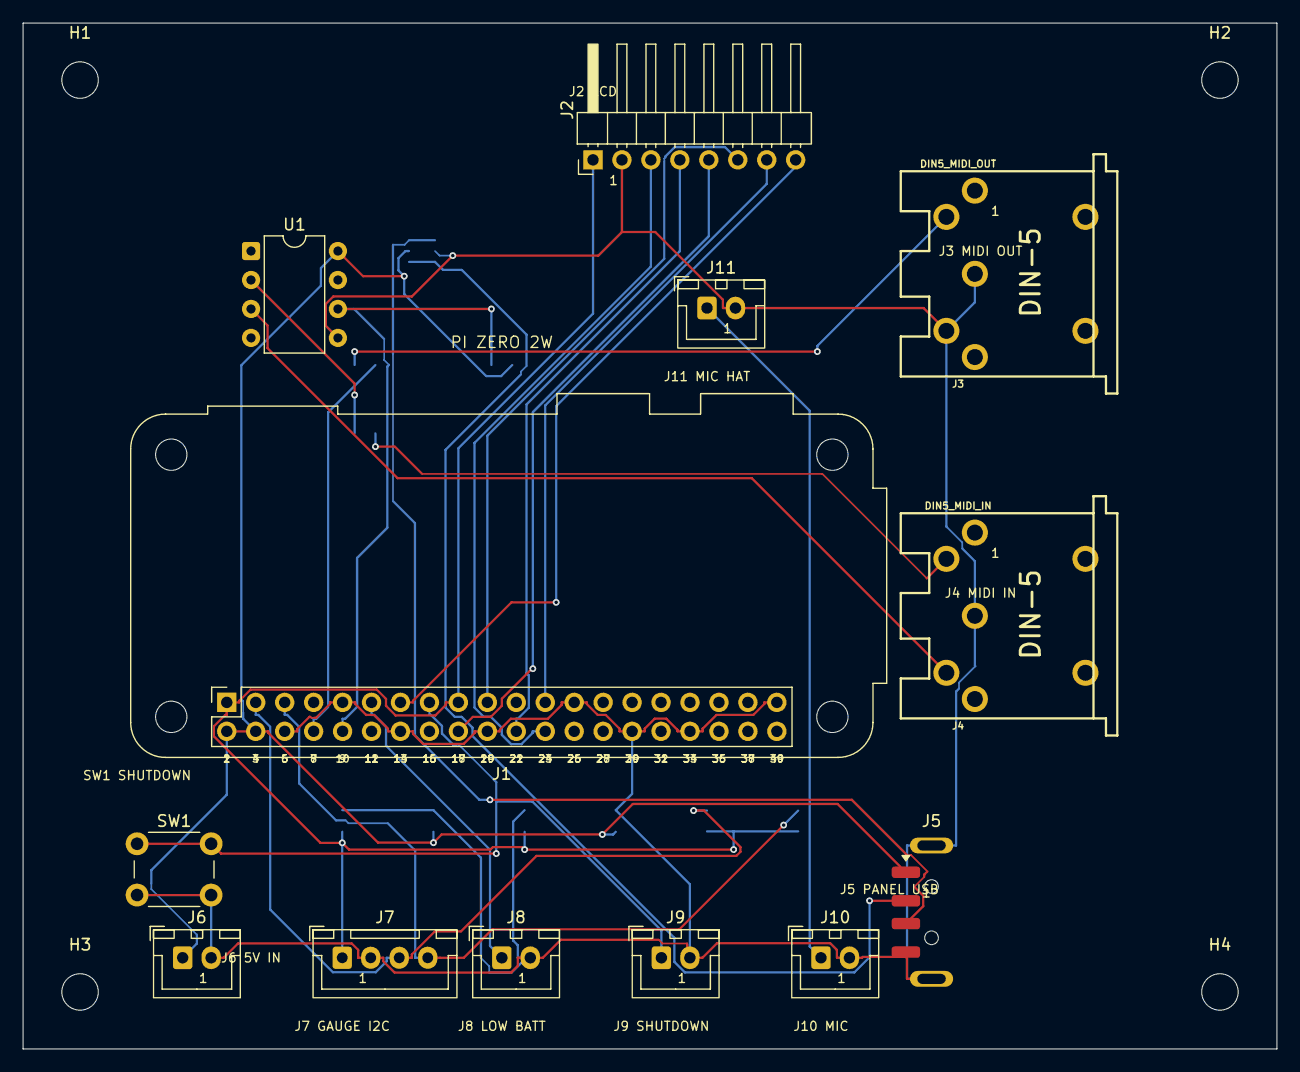
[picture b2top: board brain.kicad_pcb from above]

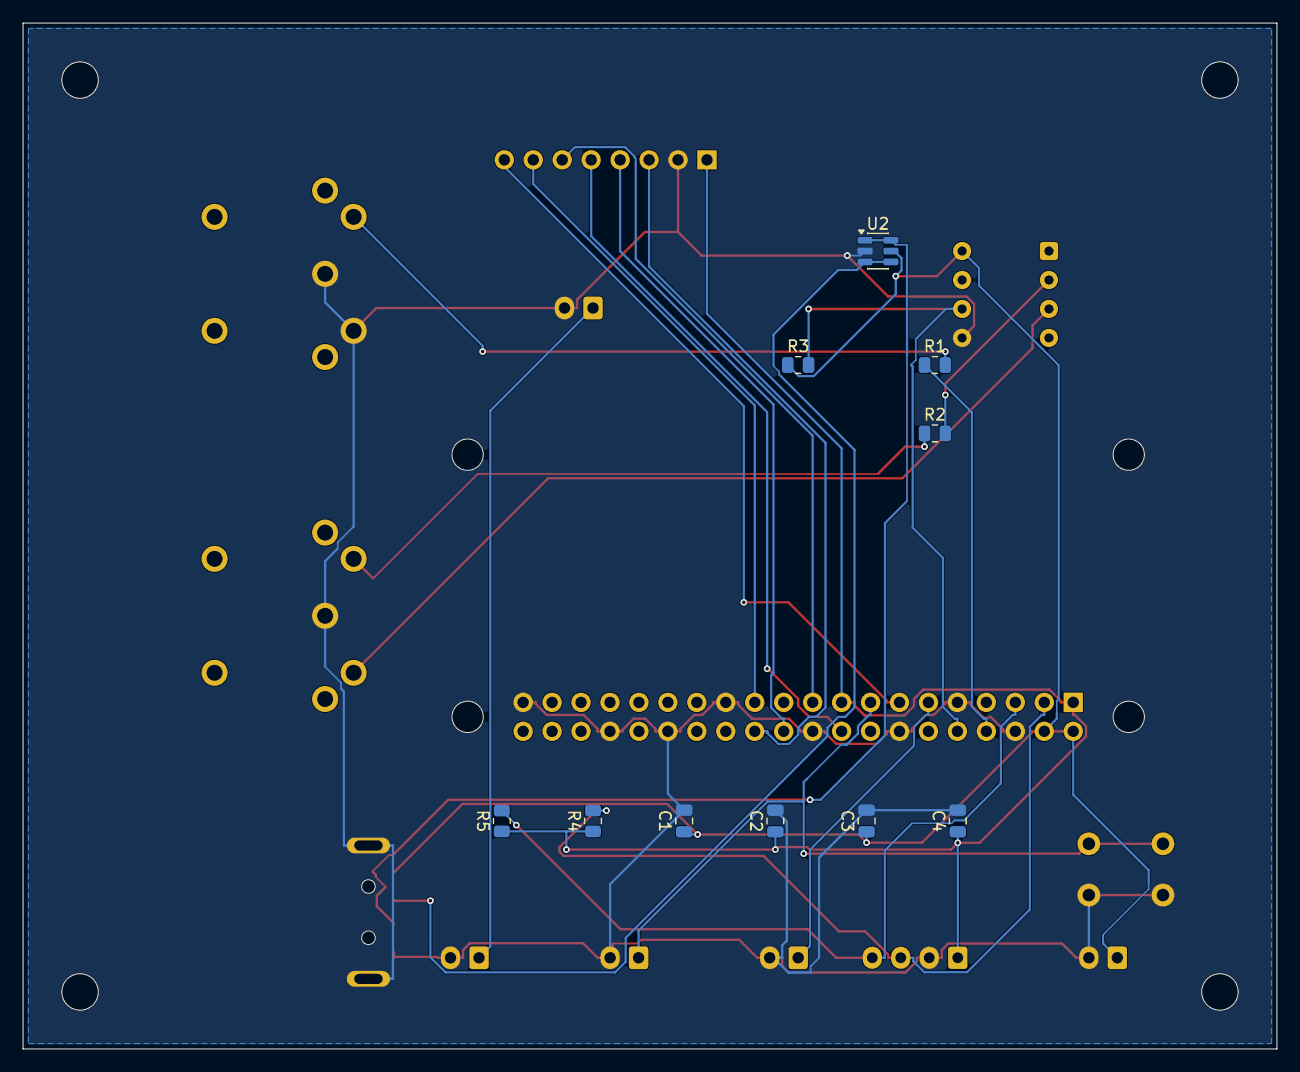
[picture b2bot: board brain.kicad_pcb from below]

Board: 2 copper layers, 110.0 x 90.0 mm, 27 parts (10 on the bottom side), 22 nets.

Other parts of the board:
H1, H2, H3, H4: MountingHole_3.2mm_M3
